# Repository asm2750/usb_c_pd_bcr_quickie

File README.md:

# USB-C PD Barrel Connector Replacement

A USB-C Power Delivery BCR Example Design:
* Based on example design from the CYPD 3177 Datasheet
* Configurable output voltage and current with resistors
* Header included for additional configuration

# WHY?
I needed a 9V wall wart for a device I recently acquired. Instead of buying another wall wart I wanted to leverage the many USB-C power supplies I have.

# Future Modifications
* Add a rotary switch for rapid voltage changes
* Add screw terminal option if micro-fit 3.0 connector is not available
* Design a 3D printable case
* Add proper BOM, v0.1 design was fabricated and assembled at JLCPCB

# License
Refer to the [License](LICENSE.md) for information.

# Tools Used
PCB - Kicad 8

# Fabricated Design

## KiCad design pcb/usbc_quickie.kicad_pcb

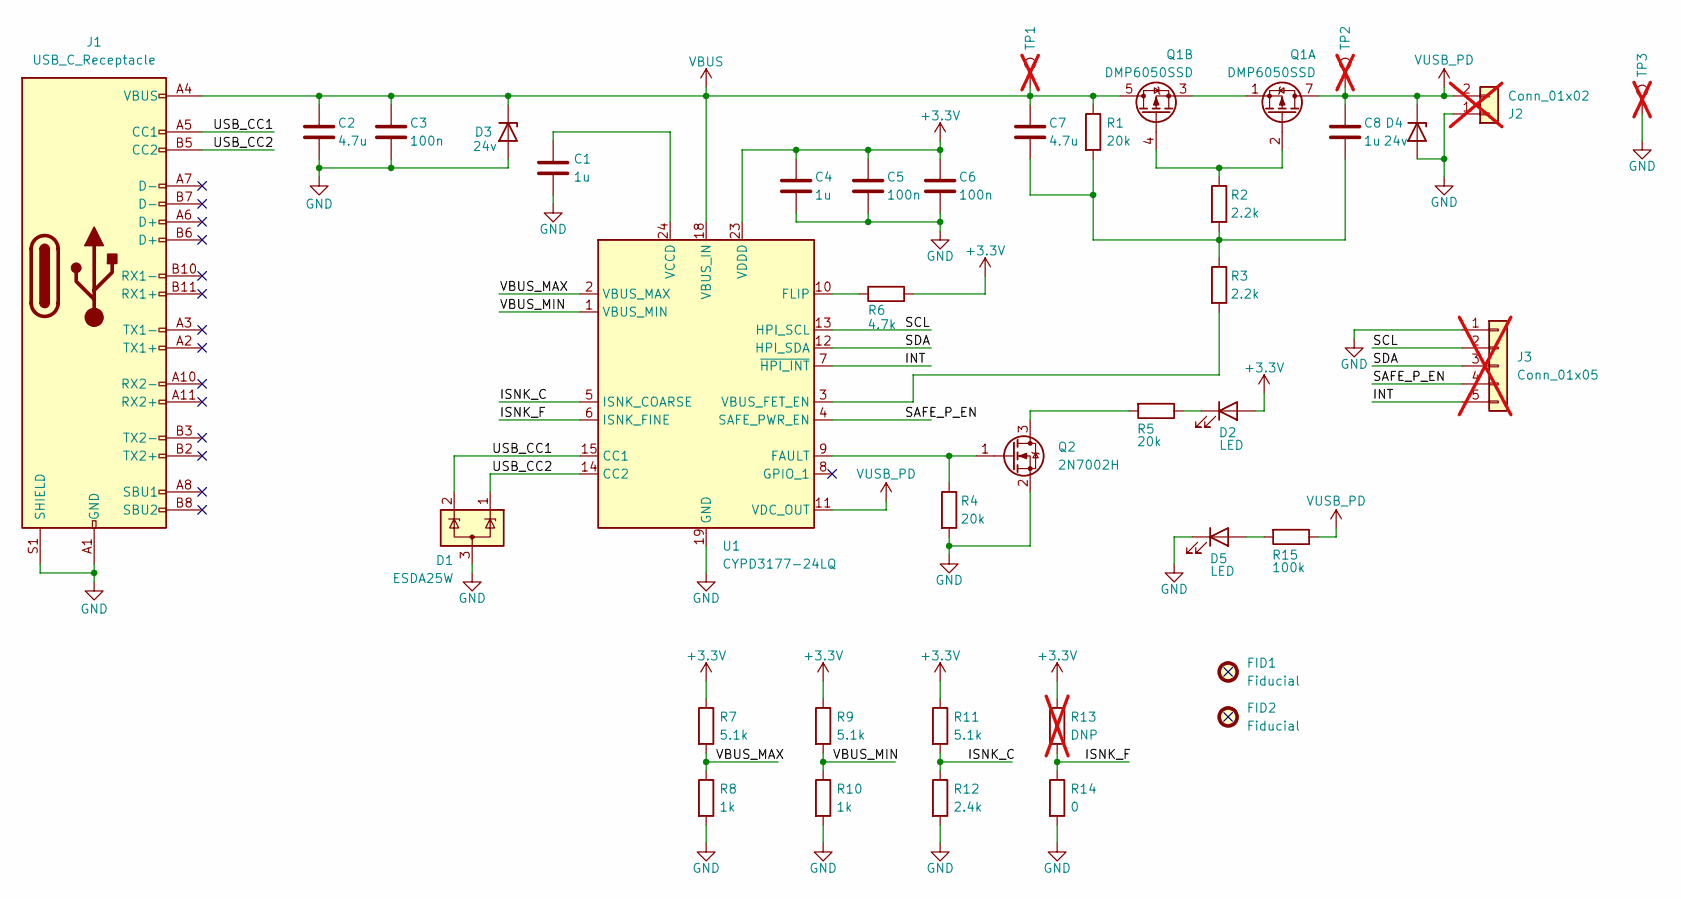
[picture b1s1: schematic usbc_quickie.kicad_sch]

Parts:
C1, C4, C8: 1u; C_0603_1608Metric; LCSC PN (Sub) C77046
C2, C7: 4.7u; C_0603_1608Metric; LCSC PN (Sub) C90057
C3, C5, C6: 100n; C_0603_1608Metric; LCSC PN (Sub) C354391
D1: ESDA25W; SOT-323_SC-70; LCSC PN (Sub) C3021136
D2: LED; LED_0603_1608Metric; LCSC PN (Sub) C510294
D3, D4: 24v; D_SOD-323; LCSC PN (Sub) C674401
D5: LED; LED_0603_1608Metric; LCSC PN (Sub) C3000897
FID1, FID2: Fiducial; Fiducial_0.5mm_Mask1.5mm
J1: USB_C_Receptacle; USB_C_Receptacle_Amphenol_12401610E4-2A; LCSC PN (Sub) C464604
J2: Conn_01x02; Molex_Micro-Fit_3.0_43650-0200_1x02_P3.00mm_Horizontal; not fitted
J3: Conn_01x05; PinHeader_1x05_P2.54mm_Vertical; not fitted
Q1: DMP6050SSD; SOIC-8_3.9x4.9mm_P1.27mm; LCSC PN (Sub) C531158
Q2: 2N7002H; SOT-23; LCSC PN (Sub) C672108
R1, R4, R5: 20k; R_0603_1608Metric; LCSC PN (Sub) C705889
R2, R3: 2.2k; R_0603_1608Metric; LCSC PN (Sub) C860297
R6: 4.7k; R_0603_1608Metric; LCSC PN (Sub) C705926
R7, R9, R11: 5.1k; R_0603_1608Metric_Pad0.98x0.95mm_HandSolder; LCSC PN (Sub) C860455
R8, R10: 1k; R_0603_1608Metric_Pad0.98x0.95mm_HandSolder; LCSC PN (Sub) C860716
R12: 2.4k; R_0603_1608Metric_Pad0.98x0.95mm_HandSolder; LCSC PN (Sub) C784582
R13: DNP; R_0603_1608Metric_Pad0.98x0.95mm_HandSolder; not fitted
R14: 0; R_0603_1608Metric_Pad0.98x0.95mm_HandSolder; LCSC PN (Sub) C116699
R15: 100k; R_0603_1608Metric; LCSC PN (Sub) C122538
TP1, TP2, TP3: TestPoint; Pin_D1.0mm_L10.0mm_LooseFit; not fitted
U1: CYPD3177-24LQ; QFN-24-1EP_4x4mm_P0.5mm_EP2.75x2.75mm; LCSC PN (Sub) C2959321

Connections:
+3.3V: C4.1, C5.1, C6.1, D2.2 (A), R6.2, R7.1, R9.1, R11.1, R13.1, U1.23 (VDDD)
/INT: J3.5, U1.7 (~HPI_INT)
/ISNK_C: R11.2, R12.1, U1.5 (ISNK_COARSE)
/ISNK_F: R13.2, R14.1, U1.6 (ISNK_FINE)
/SAFE_P_EN: J3.4, U1.4 (SAFE_PWR_EN)
/SCL: J3.2, U1.13 (HPI_SCL)
/SDA: J3.3, U1.12 (HPI_SDA)
/USB_CC1: D1.2 (K), J1.A5 (CC1), U1.15 (CC1)
/USB_CC2: D1.1 (K), J1.B5 (CC2), U1.14 (CC2)
/VBUS_MAX: R7.2, R8.1, U1.2 (VBUS_MAX)
/VBUS_MIN: R9.2, R10.1, U1.1 (VBUS_MIN)
GND: C1.2, C2.2, C3.2, C4.2, C5.2, C6.2, D1.3 (A), D3.2 (A), D4.2 (A), D5.1 (K), J1.A1 (GND), J1.A12 (GND), J1.B1 (GND), J1.B12 (GND), J1.S1 (SHIELD), J2.1, J3.1, Q2.2 (S), R4.2, R8.2, R10.2, R12.2, R14.2, TP3.1, U1.19 (GND), U1.22 (GND), U1.25 (GND)
unnamed: C7.2, C8.2, R1.2, R2.2, R3.1
unnamed: D2.1 (K), R5.1
unnamed: D5.2 (A), R15.2
unnamed: Q1.2 (G1), Q1.4 (G2), R2.1
unnamed: Q1.1 (S1), Q1.3 (S2)
unnamed: Q2.3 (D), R5.2
unnamed: Q2.1 (G), R4.1, U1.9 (FAULT)
unnamed: R6.1, U1.10 (FLIP)
unnamed: R3.2, U1.3 (VBUS_FET_EN)
unnamed: C1.1, U1.24 (VCCD)
VBUS: C2.1, C3.1, C7.1, D3.1 (K), J1.A4 (VBUS), J1.A9 (VBUS), J1.B4 (VBUS), J1.B9 (VBUS), Q1.5 (D2), Q1.6 (D2), R1.1, TP1.1, U1.18 (VBUS_IN)
VUSB_PD: C8.1, D4.1 (K), J2.2, Q1.7 (D1), Q1.8 (D1), R15.1, TP2.1, U1.11 (VDC_OUT)

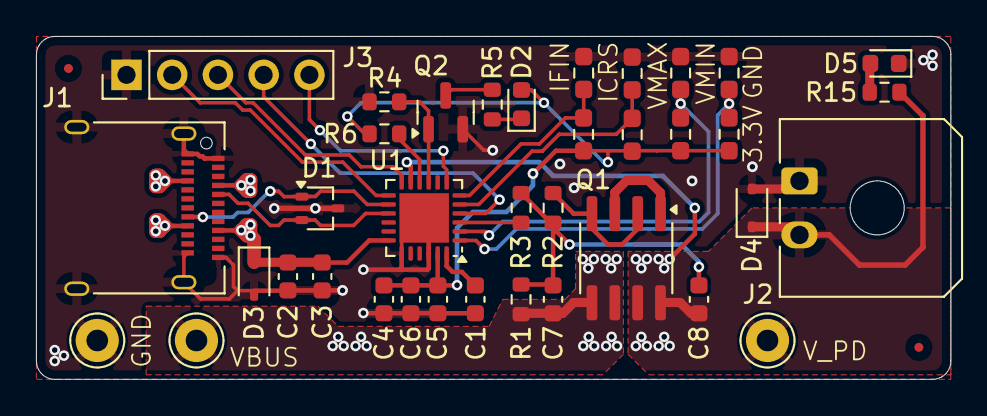
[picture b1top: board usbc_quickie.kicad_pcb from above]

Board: 2 copper layers, 50.8 x 19.0 mm, 39 parts (0 on the bottom side), 24 nets.

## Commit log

2024-10-26 Initial commit of Kicad project
